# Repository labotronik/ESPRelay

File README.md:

# ESPRelay4

Documentation rapide d'utilisation de la carte relais (Ethernet, MQTT, Wi-Fi AP fallback, BLE) d'après le firmware actuel.

## 1) Démarrage et accès

- Le serveur HTTP écoute sur le port `80`.
- La page web principale est servie sur `/`.
- Réseau Ethernet W5500 actif au boot.

Configuration réseau par défaut (si aucun fichier de config):
- IP: `192.168.1.50`
- GW: `192.168.1.1`
- Mask: `255.255.255.0`
- DNS: `192.168.1.1`

## 2) API HTTP disponible

Endpoints principaux:
- `GET /api/state` -> état courant (inputs, relays, overrides, modules, réseau, volets, etc.)
- `GET /api/rules` -> règles simples + volets
- `GET /api/net` -> config réseau
- `GET /api/wifi` -> config/status Wi-Fi AP
- `GET /api/mqtt` -> config/status MQTT (transport actif, état GSM)
- `GET /api/backup` -> backup global
- `PUT /api/rules` -> applique des règles
- `PUT /api/net` -> applique réseau
- `PUT /api/wifi` -> active/désactive AP Wi-Fi
- `PUT /api/mqtt` -> applique config MQTT
- `POST /api/override` -> force un relais (`AUTO|FORCE_ON|FORCE_OFF`)
- `POST /api/shutter` -> commande volet (`UP|DOWN|STOP|AUTO`)
- `POST /api/ota` -> OTA firmware binaire
- `POST /api/otafs` -> OTA LittleFS binaire

Authentification:
- Défaut: `admin / admin`
- API de changement: `PUT /api/auth`

## 3) Utilisation MQTT (Ethernet + fallback GSM)

### 3.1 Principe de transport

Le firmware peut utiliser:
- broker local (Ethernet)
- broker GSM (A7670 + 1NCE)

Comportement actuel recommandé:
- tentative sur broker local d'abord
- si échec local, fallback sur broker GSM public (`gsm_mqtt_host`)

### 3.2 Paramètres MQTT (via `PUT /api/mqtt`)

Champs utiles:
- `enabled`: `1` pour activer MQTT
- `transport`: `ethernet`, `auto` ou `gsm`
- `host`, `port`, `user`, `pass`: broker principal (local)
- `gsm_mqtt_host`, `gsm_mqtt_port`, `gsm_mqtt_user`, `gsm_mqtt_pass`: broker GSM
- `client_id`: identifiant MQTT
- `base`: base topic (ex: `esprelay4`)
- `retain`: `1` recommandé pour récupérer un état immédiatement après subscribe
- `apn`, `gsm_user`, `gsm_pass`: paramètres data opérateur GSM

Exemple minimal:
```json
{
  "enabled": 1,
  "transport": "ethernet",
  "host": "192.168.1.43",
  "port": 1883,
  "gsm_mqtt_host": "82.64.24.196",
  "gsm_mqtt_port": 1883,
  "client_id": "ESPRelay4",
  "base": "esprelay4",
  "retain": 1,
  "apn": "iot.1nce.net",
  "gsm_user": "",
  "gsm_pass": ""
}
```

### 3.3 Commandes MQTT relais

Base topic par défaut: `esprelay4`

Relais 1:
- commande: `esprelay4/relay/1/set`
- payload: `ON`, `OFF`, `AUTO`, `TOGGLE`
- état: `esprelay4/relay/1/state`

Exemples:
```bash
mosquitto_sub -h 82.64.24.196 -p 1883 -t esprelay4/relay/1/state -v
mosquitto_pub -h 82.64.24.196 -p 1883 -t esprelay4/relay/1/set -m ON
```

Important:
- Si un relais est réservé à un volet, les overrides directs sont refusés/ignorés.
- `set ON/OFF` force le relais (override) tant que `AUTO` n'est pas envoyé.

### 3.4 Keepalive MQTT

- Paramètre firmware: `MQTT_KEEPALIVE_SECONDS`
- Valeur actuelle: `1800` secondes (30 min)

### 3.5 Mode GSM économie data

Quand transport actif = GSM:
- publication limitée aux états de pilotage utiles
- pas de discovery Home Assistant en boucle
- pas de télémétrie non essentielle en continu

## 4) Wi-Fi (AP fallback)

Le Wi-Fi est utilisé ici en mode AP local de maintenance.

- AP SoftAP activable/désactivable via `/api/wifi` ou MQTT:
  - `esprelay4/wifi/ap/set` avec payload `ON` ou `OFF`
- SSID par défaut: basé sur l'identifiant de la carte (`ESPRelay4-XXXXXX`)
- Mot de passe par défaut: `esprelay4`
- Captive portal simplifié (redirections vers l'IP AP)

## 5) BLE

Le firmware expose l'état en BLE (NimBLE):
- Device name: similaire au SSID (`ESPRelay4-XXXXXX`)
- Service UUID dynamique basé sur MAC:
  - `6E400001-B5A3-F393-E0A9-XXXXXXXXXXXX`
- Characteristic notify/read:
  - `6E400003-B5A3-F393-E0A9-XXXXXXXXXXXX` (READ + NOTIFY)
- Characteristic read:
  - `6E400004-B5A3-F393-E0A9-XXXXXXXXXXXX` (READ)

Particularités flux notify:
- cadence ~1 Hz
- tramage: `0x1E 0x1E + payload JSON + 0x1F`
- chunk BLE max ~160 bytes

Activation BLE:
- via MQTT: `esprelay4/ble/set` avec `ON`/`OFF`
- via API config BLE (`/ble.json`)

## 6) Règles / Volets / Priorités

Ordre de priorité des sorties:
1. Règles simples
2. Logique volet (si relais réservés)
3. Override manuel (MQTT/API) sur relais non réservés
4. Sécurité finale interlock volet

Conséquence:
- un `relay/x/set ON` écrase la règle tant que `AUTO` n'est pas renvoyé
- sur relais réservé volet: override interdit

## 7) Factory reset

- Maintenir le bouton factory (`IO0`) pendant ~10 secondes au boot
- Supprime les fichiers config: `/net.json`, `/mqtt.json`, `/rules.json`, `/auth.json`, `/wifi.json`, `/ble.json`
- Redémarrage automatique

## 8) Estimation conso data GSM

Hypothèses:
- Forfait: 500 Mo sur 10 ans
- Conso idle estimée: 10 Ko/jour
- 1 activation relais + lecture d'état MQTT: ~0,3 Ko

Seuil moyen:
- 500 Mo / 10 ans ~= 140 Ko/jour
- Après idle (10 Ko/jour), il reste ~130 Ko/jour pour les actions

Cas d'usage pouvant vider 500 Mo:
- ~430 activations/jour avec lecture d'état, sur la durée
- ou moins si réseau instable (reconnexions MQTT fréquentes)
- OTA via GSM: plusieurs Mo ponctuels

Exemple à risque:
- ~150 activations/jour + ~10 à 15 reconnexions MQTT/jour sur la durée

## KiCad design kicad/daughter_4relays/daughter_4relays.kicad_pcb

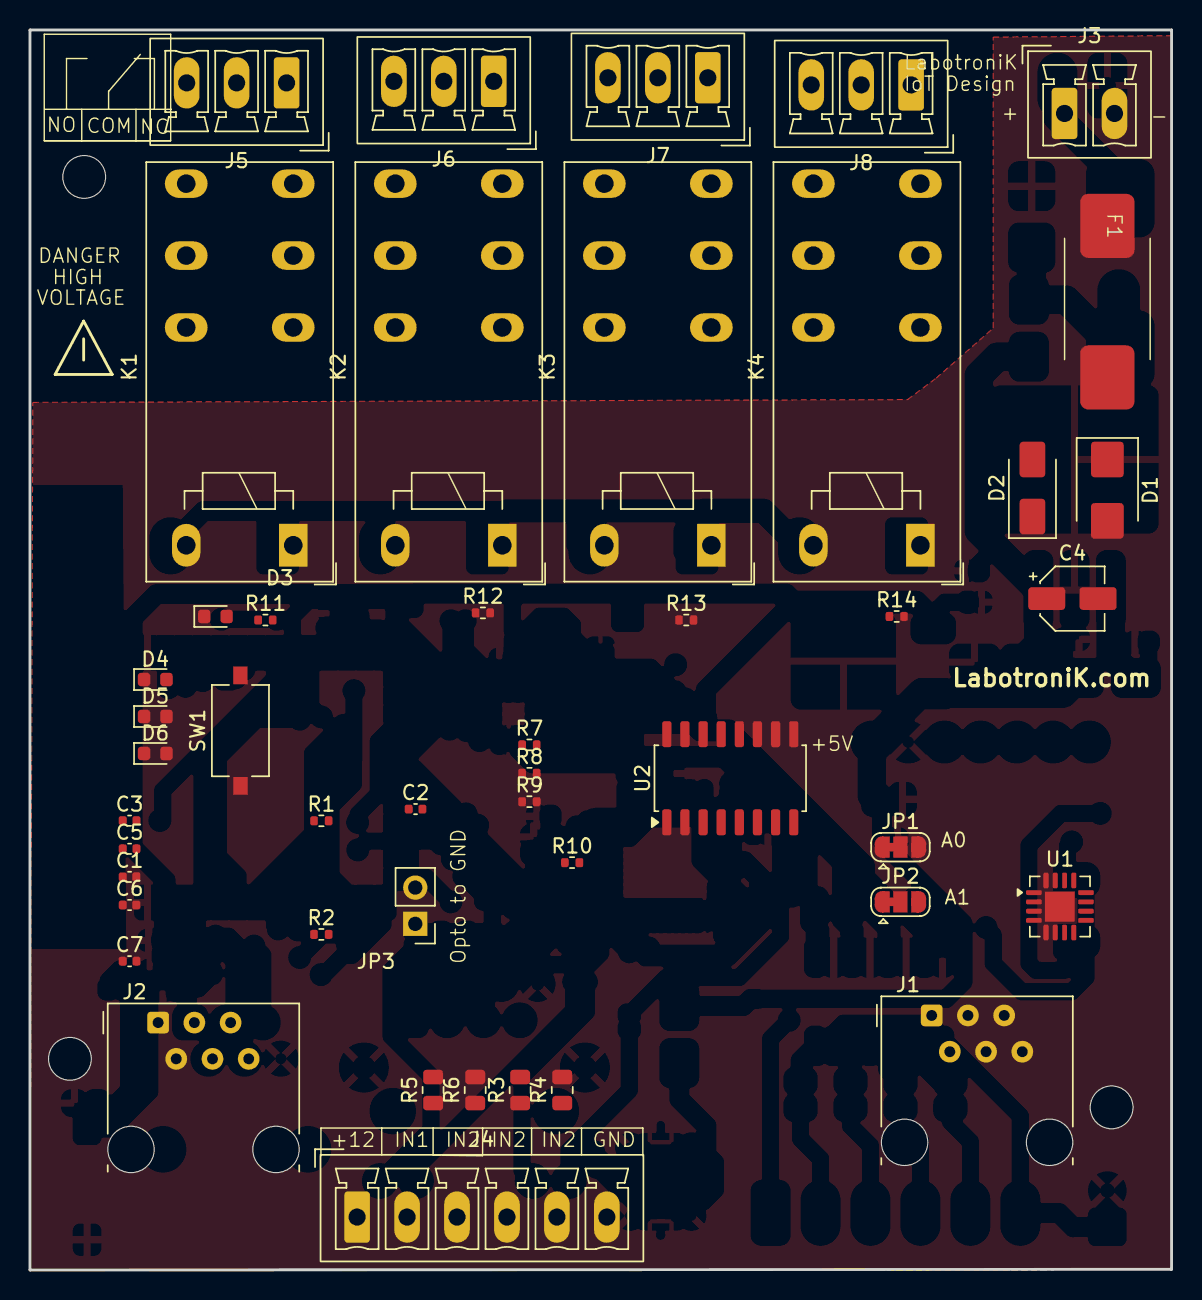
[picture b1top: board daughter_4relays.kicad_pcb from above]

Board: 2 copper layers, 80.0 x 86.9 mm, 46 parts (0 on the bottom side), 47 nets, no tracks yet.

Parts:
C1, C2, C3, C5, C6, C7: 100nF; C_0402_1005Metric
C4: 10µF; CP_Elec_4x5.4
D1: SMBJ12A; D_SMB
D2: B230A-13-F; D_SMA
D3, D4, D5, D6: LED LTST-C193TGKT-5A; LED_0603_1608Metric
F1: Fuse 3A; 0154250DR littelfuse 10.62 3.81
J1, J2: RJ12; RJ12_Amphenol_54601-x06_Horizontal
J3: POWER_INPUT; PhoenixContact_MCV_1,5_2-G-3.5_1x02_P3.50mm_Vertical
J4: Screw_Terminal_01x06; PhoenixContact_MCV_1,5_6-G-3.5_1x06_P3.50mm_Vertical
J5, J6, J7, J8: Screw_Terminal_01x03; PhoenixContact_MCV_1,5_3-G-3.5_1x03_P3.50mm_Vertical
JP1, JP2: SolderJumper_3_Bridged12; SolderJumper-3_P1.3mm_Bridged12_RoundedPad1.0x1.5mm
JP3: Jumper_2_Bridged; PinHeader_1x02_P2.54mm_Vertical
K1, K2, K3, K4: RZ03-1C4-D012; Relay_SPDT_Schrack-RT1-16A-FormC_RM5mm
R1, R2: 10k; R_0402_1005Metric
R3, R4, R5, R6: 2.2k; R_0805_2012Metric
R7, R8, R9, R10: 4k7; R_0402_1005Metric
R11, R12, R13, R14: 680; R_0402_1005Metric
SW1: SW_Push; SW_Tactile_SPST_NO_Straight_CK_PTS636Sx25SMTRLFS
U1: PCA9538BS; NXP_VQFN-16-1EP_4x4mm_P0.65mm_EP2.1x2.1mm
U2: TCMT4100; SOP-16_4.4x10.4mm_P1.27mm

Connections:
+3.3V: C1.1, C2.1, C6.1, J1.1, J2.1, JP1.3 (B), JP2.3 (B), R1.1, R2.2, R7.1, R8.1, R9.1, R10.1, U1.14 (V_{DD})
+12V: C4.1, C5.1, C7.1, D2.1 (K), J4.1
/IO1: J1.4, J2.4
/IO2: J1.5, J2.5
/SCL: J1.3, J2.3, U1.12 (SCL)
/SDA: J1.2, J2.2, U1.13 (SDA)
/input/IN1: J4.2, R5.1
/input/IN2: J4.3, R6.1
/input/IN3: J4.4, R3.1
/input/IN4: J4.5, R4.1
/input/OPTO_GND: J4.6, JP3.1 (A), U2.2, U2.4, U2.6, U2.8
/input/input1: R8.2, U1.7 (IO4), U2.16
/input/input2: R9.2, U1.8 (IO5), U2.14
/input/input3: R7.2, U1.9 (IO6), U2.12
/input/input4: R10.2, U1.10 (IO7), U2.10
/relais/PWR_KM1: K1.A1, R11.1
/relais/PWR_KM2: K2.A1, R12.1
/relais/PWR_KM3: K3.A1, R13.1
/relais/PWR_KM4: K4.A1, R14.1
GND: C1.2, C2.2, C3.2, C6.2, C7.2, D3.1 (K), D4.1 (K), D5.1 (K), D6.1 (K), J1.6, J2.6, JP1.1 (A), JP2.1 (A), JP3.2 (B), K1.A2, K2.A2, K3.A2, K4.A2, SW1.1, U1.6 (V_{SS}), U1.17 (V_{SS}), U2.9, U2.11, U2.13, U2.15
unnamed: C3.1, R1.2, SW1.2
unnamed: D1.1 (A1), D2.2 (A), F1.2
unnamed: C4.2, C5.2, D1.2 (A2), J3.1
unnamed: D3.2 (A), R11.2
unnamed: D4.2 (A), R12.2
unnamed: D5.2 (A), R13.2
unnamed: D6.2 (A), R14.2
unnamed: F1.1, J3.2
unnamed: J5.1, K1.12
unnamed: J5.2, K1.11
unnamed: J5.3, K1.14
unnamed: J6.1, K2.12
unnamed: J6.2, K2.11
unnamed: J6.3, K2.14
unnamed: J7.1, K3.12
unnamed: J7.2, K3.11
unnamed: J7.3, K3.14
unnamed: J8.1, K4.12
unnamed: J8.2, K4.11
unnamed: J8.3, K4.14
unnamed: JP1.2 (C), U1.15 (A0)
unnamed: JP2.2 (C), U1.16 (A1)
unnamed: R3.2, U2.5
unnamed: R4.2, U2.7
unnamed: R5.2, U2.1
unnamed: R6.2, U2.3
unnamed: R2.1, U1.1 (~RESET)

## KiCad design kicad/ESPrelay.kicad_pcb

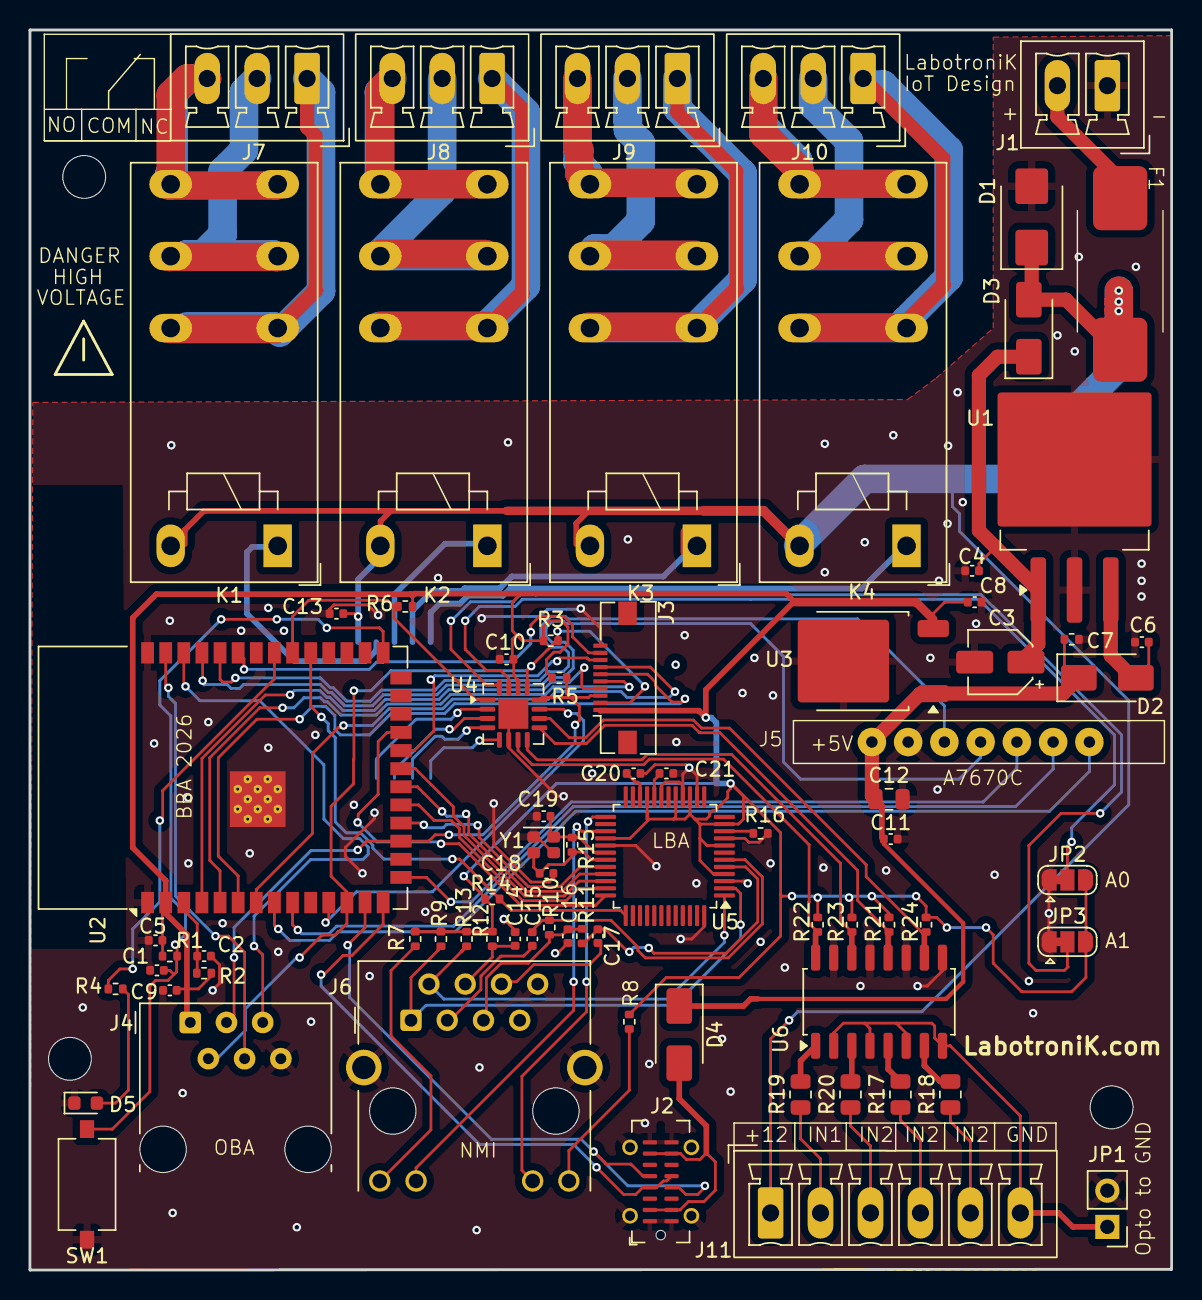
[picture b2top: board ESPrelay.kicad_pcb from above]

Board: 2 copper layers, 80.0 x 86.9 mm, 78 parts (1 on the bottom side), 89 nets.

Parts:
C1, C2, C4, C5, C6, C8, C9, C10, C11, C13: 100nF; C_0402_1005Metric
C3: 10µF; CP_Elec_4x5.4
C7: 10nF; R_0402_1005Metric
C12: 10µF; C_0805_2012Metric
C14: 22nF; C_0402_1005Metric
C15, C17: 6.8nF; C_0402_1005Metric
C16, C20: 10nF; C_0402_1005Metric
C18, C19: 12pF; C_0402_1005Metric
C21: 4.7µF; C_0402_1005Metric
D1: SMBJ12A; D_SMB
D2, D3, D4: B230A-13-F; D_SMA
D5: LED LTST-C193TGKT-5A; LED_0603_1608Metric
F1: Fuse 3A; 0154250DR littelfuse 10.62 3.81
J1: POWER_INPUT; PhoenixContact_MCV_1,5_2-G-3.5_1x02_P3.50mm_Vertical
J2: GT-USB-7051A; USB_C_Receptacle_G-Switch_GT-USB-7051x
J3: MOLEX 545480671; Molex_54548-1071_1x10-1MP_P0.5mm_Horizontal
J4: RJ12; RJ12_Amphenol_54601-x06_Horizontal
J5: A7670C MODULE; a7670c module
J6: HR911105A; RJ45_Hanrun_HR911105A_Horizontal
J7, J8, J9, J10: Screw_Terminal_01x03; PhoenixContact_MCV_1,5_3-G-3.5_1x03_P3.50mm_Vertical
J11: Screw_Terminal_01x06; PhoenixContact_MCV_1,5_6-G-3.5_1x06_P3.50mm_Vertical
JP1: Jumper_2_Bridged; PinHeader_1x02_P2.54mm_Vertical
JP2, JP3: SolderJumper_3_Bridged12; SolderJumper-3_P1.3mm_Bridged12_RoundedPad1.0x1.5mm
K1, K2, K3, K4: RZ03-1C4-D012; Relay_SPDT_Schrack-RT1-16A-FormC_RM5mm
Q1: TBD62083AFG_EL; SOIC127P1030X245-18N
R1, R2, R6: 10k; R_0402_1005Metric
R3, R5, R21, R22, R23, R24: 4k7; R_0402_1005Metric
R4: 680; R_0402_1005Metric
R7, R8, R14: 1k; R_0402_1005Metric
R9, R10, R11, R13: 49.9; R_0402_1005Metric
R12: 10; R_0402_1005Metric
R15: 1M; R_0402_1005Metric
R16: 12.4k 1%; R_0402_1005Metric
R17, R18, R19, R20: 2.2k; R_0805_2012Metric
SW1: SW_Push; SW_Tactile_SPST_NO_Straight_CK_PTS636Sx25SMTRLFS
U1: MC7805BD2TR4G; TO-263-3_TabPin2
U2: ESP32-S3-WROOM-1-N4; ESP32-S3-WROOM-1
U3: LF33CDT-TR; TO-252-2
U4: PCA9538BS; NXP_VQFN-16-1EP_4x4mm_P0.65mm_EP2.1x2.1mm
U5: W5500; LQFP-48_7x7mm_P0.5mm
U6: TCMT4100; SOP-16_4.4x10.4mm_P1.27mm
Y1: X201625MOB4SI - 25Mhz; Crystal_SMD_2016-4Pin_2.0x1.6mm

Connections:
+3.3V: C5.1, C8.1, C9.1, C10.1, J3.1, J4.1, JP2.3 (B), JP3.3 (B), R1.1, R2.1, R3.2, R5.2, R6.2, R7.1, R8.2, R9.2, R12.2, R13.2, R14.1, R21.1, R22.1, R23.1, R24.1, U2.2 (3V3), U3.3 (VO), U4.14 (V_{DD}), U5.4 (AVDD), U5.8 (AVDD), U5.11 (AVDD), U5.15 (AVDD), U5.17 (AVDD), U5.21 (AVDD), U5.28 (VDD)
+5V: C7.1, C11.1, C12.1, D2.1 (K), D4.1 (K), J5.1, U3.1 (VI)
+12V: C13.1, D1.1 (A1), D3.2 (A), F1.2, J11.1, K1.A2, K2.A2, K3.A2, K4.A2, Q1.10 (COMMON)
/BP1: J3.4, U2.4 (IO4)
/BP2: J3.5, U2.5 (IO5)
/BP3: J3.6, U2.6 (IO6)
/BP4: J3.7, U2.7 (IO7)
/BP5: J3.8, U2.22 (IO14)
/COM_BP: J3.9, U2.35 (IO42)
/D+: J2.A6 (D+), J2.B6 (D+), U2.14 (USB_D+)
/D-: J2.A7 (D-), J2.B7 (D-), U2.13 (USB_D-)
/ETH_INT: U2.23 (IO21), U5.36 (~INT)
/ETH_RESET: R14.2, U2.31 (IO38), U5.37 (~RST)
/IO1: J4.4, U2.39 (IO1)
/IO2: J4.5, U2.38 (IO2)
/MCP_RESET: R6.1, U2.32 (IO39), U4.1 (~RESET)
/Net: J5.6, U2.9 (IO16)
/Pen: J5.5, U2.15 (IO3)
/Pwk: J5.7, U2.8 (IO15)
/Rx: J5.4, U2.37 (TXD0)
/SCL: J3.3, J4.3, R5.1, U2.17 (IO9), U4.12 (SCL)
/SDA: J3.2, J4.2, R3.1, U2.12 (IO8), U4.13 (SDA)
/Tx: J5.3, U2.36 (RXD0)
/input/IN1: J11.2, R19.1
/input/IN2: J11.3, R20.1
/input/IN3: J11.4, R17.1
/input/IN4: J11.5, R18.1
/input/OPTO_GND: J11.6, JP1.1 (A), U6.2, U6.4, U6.6, U6.8
/input/input1: R22.2, U4.7 (IO4), U6.16
/input/input2: R23.2, U4.8 (IO5), U6.14
/input/input3: R21.2, U4.9 (IO6), U6.12
/input/input4: R24.2, U4.10 (IO7), U6.10
/relais/PWR_KM1: K1.A1, Q1.11 (O8)
/relais/PWR_KM2: K2.A1, Q1.12 (O7)
/relais/PWR_KM3: K3.A1, Q1.13 (O6)
/relais/PWR_KM4: K4.A1, Q1.14 (O5)
/w5500/ETH_CS: U2.18 (IO10), U5.32 (~SCS)
/w5500/ETH_MISO: U2.21 (IO13), U5.34 (MISO)
/w5500/ETH_MOSI: U2.19 (IO11), U5.35 (MOSI)
/w5500/ETH_SCLK: U2.20 (IO12), U5.33 (SCLK)
/w5500/RCT: C16.2, J6.5 (RCT), R10.2, R11.1
/w5500/RXN: C17.1, R11.2, U5.5 (RXN)
/w5500/RXNNET: C17.2, J6.6 (RD-)
/w5500/RXP: C15.1, R10.1, U5.6 (RXP)
/w5500/RXPNET: C15.2, J6.3 (RD+)
/w5500/TCT: C14.2, J6.4 (TCT), R12.1
/w5500/TXN: J6.2 (TD-), R13.1, U5.1 (TXN)
/w5500/TXP: J6.1 (TD+), R9.1, U5.2 (TXP)
/w5500/XI: C19.2, R15.2, U5.30 (XI/CLKIN), Y1.1
/w5500/XO: C18.2, R15.1, U5.31 (XO), Y1.3
/w5500/act_led: J6.10, U5.27 (ACTLED)
/w5500/link_led: J6.11, U5.25 (LINKLED)
GND: C1.2, C2.2, C3.2, C4.2, C5.2, C6.2, C7.2, C8.2, C9.2, C10.2, C11.2, C12.2, C13.2, C14.1, C16.1, C18.1, C19.1, C20.2, C21.2, D1.2 (A2), D5.1 (K), J1.1, J2.A1 (GND), J2.A12 (GND), J2.B1 (GND), J2.B12 (GND), J2.S1 (SHIELD), J3.10, J4.6, J5.2, J6.8, J6.SH, JP1.2 (B), JP2.1 (A), JP3.1 (A), Q1.9 (GND), R16.2, SW1.1, U1.2 (GND), U2.1 (GND), U2.40 (GND), U2.41 (GND), U3.2 (GND), U4.6 (V_{SS}), U4.17 (V_{SS}), U5.3 (AGND), U5.9 (AGND), U5.14 (AGND), U5.16 (AGND), U5.19 (AGND), U5.29 (GND), U5.48 (AGND), U6.9, U6.11, U6.13, U6.15, Y1.2, Y1.4
unnamed: C6.1, D2.2 (A), U1.3 (OUT)
unnamed: C3.1, C4.1, D3.1 (K), U1.1 (IN)
unnamed: D4.2 (A), J2.A4 (VBUS), J2.A9 (VBUS), J2.B4 (VBUS), J2.B9 (VBUS)
unnamed: D5.2 (A), R4.2
unnamed: F1.1, J1.2
unnamed: J6.9, R7.2
unnamed: J6.12, R8.1
unnamed: J7.1, K1.12
unnamed: J7.2, K1.11
unnamed: J7.3, K1.14
unnamed: J8.1, K2.12
unnamed: J8.2, K2.11
unnamed: J8.3, K2.14
unnamed: J9.1, K3.12
unnamed: J9.2, K3.11
unnamed: J9.3, K3.14
unnamed: J10.1, K4.12
unnamed: J10.2, K4.11
unnamed: J10.3, K4.14
unnamed: JP2.2 (C), U4.15 (A0)
unnamed: JP3.2 (C), U4.16 (A1)
unnamed: Q1.5 (I5), U4.5 (IO3)
unnamed: Q1.6 (I6), U4.4 (IO2)
unnamed: Q1.7 (I7), U4.3 (IO1)
unnamed: Q1.8 (I8), U4.2 (IO0)
unnamed: R17.2, U6.5
unnamed: R18.2, U6.7
unnamed: R19.2, U6.1
unnamed: R20.2, U6.3
unnamed: C2.1, R2.2, U2.3 (EN)
unnamed: C1.1, R1.2, SW1.2, U2.27 (IO0)
unnamed: U2.11 (IO18), U4.11 (~INT)
unnamed: R4.1, U2.33 (IO40)
unnamed: C20.1, U5.22 (1V2O)
unnamed: R16.1, U5.10 (EXRES1)
unnamed: C21.1, U5.20 (TOCAP)

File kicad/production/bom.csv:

Designator,Footprint,Quantity,Value,LCSC Part #
"C1, C10, C11, C13, C2, C4, C5, C6, C8, C9",0402,10,100nF,
C12,0805,1,10µF,
C14,0402,1,22nF,
"C15, C17",0402,2,6.8nF,
"C16, C20, C7",0402,3,10nF,
"C18, C19",0402,2,12pF,
C21,0402,1,4.7µF,
C3,CP_Elec_4x5.4,1,10µF,
D1,D_SMB,1,SMBJ12A,
"D2, D3, D4",D_SMA,3,B230A-13-F,
D5,0603,1,LED LTST-C193TGKT-5A,
F1,0154250DR littelfuse 10.62 3.81,1,Fuse 3A,
J1,"PhoenixContact_MCV_1,5_2-G-3.5_1x02_P3.50mm_Vertical",1,POWER_INPUT,
"J10, J7, J8, J9","PhoenixContact_MCV_1,5_3-G-3.5_1x03_P3.50mm_Vertical",4,Screw_Terminal_01x03,
J11,"PhoenixContact_MCV_1,5_6-G-3.5_1x06_P3.50mm_Vertical",1,Screw_Terminal_01x06,
J2,USB_C_Receptacle_G-Switch_GT-USB-7051x,1,GT-USB-7051A,
J3,Molex_54548-1071_1x10-1MP_P0.5mm_Horizontal,1,MOLEX 545480671,
J4,RJ12_Amphenol_54601-x06_Horizontal,1,RJ12,
J5,a7670c module,1,A7670C MODULE,
J6,RJ45_Hanrun_HR911105A_Horizontal,1,HR911105A,
JP1,PinHeader_1x02_P2.54mm_Vertical,1,Jumper_2_Bridged,
"K1, K2, K3, K4",Relay_SPDT_Schrack-RT1-16A-FormC_RM5mm,4,RZ03-1C4-D012,
Q1,SOIC127P1030X245-18N,1,TBD62083AFG_EL,
"R1, R2, R6",0402,3,10k,
"R10, R11, R13, R9",0402,4,49.9,
R12,0402,1,10,
"R14, R7, R8",0402,3,1k,
R15,0402,1,1M,
R16,0402,1,12.4k 1%,
"R17, R18, R19, R20",0805,4,2.2k,
"R21, R22, R23, R24, R3, R5",0402,6,4k7,
R4,0402,1,680,
SW1,SW_Tactile_SPST_NO_Straight_CK_PTS636Sx25SMTRLFS,1,SW_Push,
U1,TO-263-3_TabPin2,1,MC7805BD2TR4G,
U2,ESP32-S3-WROOM-1,1,ESP32-S3-WROOM-1-N4,
U3,TO-252-2,1,LF33CDT-TR,
U4,NXP_VQFN-16-1EP_4x4mm_P0.65mm_EP2.1x2.1mm,1,PCA9538BS,
U5,LQFP-48_7x7mm_P0.5mm,1,W5500,
U6,SOP-16_4.4x10.4mm_P1.27mm,1,TCMT4100,
Y1,Crystal_SMD_2016-4Pin_2.0x1.6mm,1,X201625MOB4SI - 25Mhz,

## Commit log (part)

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2025-11-03 Create test
2025-11-03 test
2026-01-07 avancement carte 4 relays
2026-01-16 stop tracking backups
2026-01-16 production 1
2026-01-30 Réorganisation : tous les fichiers déplacés dans kicad/
2026-01-30 Ajout de .gitignore pour KiCad
2026-01-30 Réorganisation : tous les fichiers dans kicad/
2026-01-30 Ajout du fichier .gitignore pour KiCad
2026-01-30 premier test web ok avant integration mqtt
2026-01-30 mqtt ok avec HA
2026-01-30 multi cartes a tester. web ok, HA ok, 2 volets OK
2026-02-01 a priori fonctionnel multi cartes (mqtt, page web, HA). a tester
2026-02-01 page de log pour modif des setup OK. ajout bouton de reset et les status pour reset firmware. a tester
2026-02-01 ajout connexion wifi
2026-02-01 modification interface web
2026-02-01 modif GUI, ajout OTA HTTP
2026-02-03 inversion inputs, modiuf UI. ok avant optimisation du code
2026-02-03 affichage erreur comm I2C module, UI: affichage fw git
2026-02-03 affichage tag fw
2026-02-04 minor bug update. add daughter pcb initial commit
2026-02-10 ajout redirection page web sur AP
2026-02-10 add BLE fuinction and flutter android app (read only)
2026-02-10 add virtual input for HA. add button for BLE/wifi
2026-02-20 feat: add GSM MQTT mode telemetry, optimize Flutter MQTT dashboard stability, and refresh app brandin
2026-03-27 chore: snapshot avant nouvelle fonctionnalite
2026-03-27 feat: stabilise MQTT auto ETH+GSM et fiabilise l'UI web
    Changements majeurs:
    - MQTT: mode transport par défaut aligné sur auto (fallback parsing + UI), avec statut UI recalculé proprement en mode auto.
    - MQTT GSM: connexion GSM considérée active uniquement si modem + data réellement UP, évite les faux états "Connected (GSM)".
    - HTTP/UI: retours d'action locaux ajoutés sur les boutons critiques (save/auth/net/rules/apply), réduction des blocages perçus côté webapp.
    - Sécurité: suppression de wifi.pass dans /api/state (endpoint non authentifié).
    - Backup restore: validation sans effets de bord + logique de rollback pour éviter les applications partielles en cas d'échec d
2026-03-30 feat: add input naming/VIN control and improve 1-Wire sensor scan
2026-03-30 MQTT: device-id MAC, base espr4, fallback GSM guardrails, and UI updates
    Firmware (ESPRelay4):\n- Use MAC12 as MQTT device ID (no ER4- prefix)\n- Default/normalized base topic set to espr4 (with legacy esprelay4 migration)\n- Fix transport normalization to keep ethernet m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
2026-03-31 feat(flutter_espr4): add BLE-aware transport sync, GSM/local recovery, VIN controls and swipe MQTT topics page
2026-03-31 app mqtt
